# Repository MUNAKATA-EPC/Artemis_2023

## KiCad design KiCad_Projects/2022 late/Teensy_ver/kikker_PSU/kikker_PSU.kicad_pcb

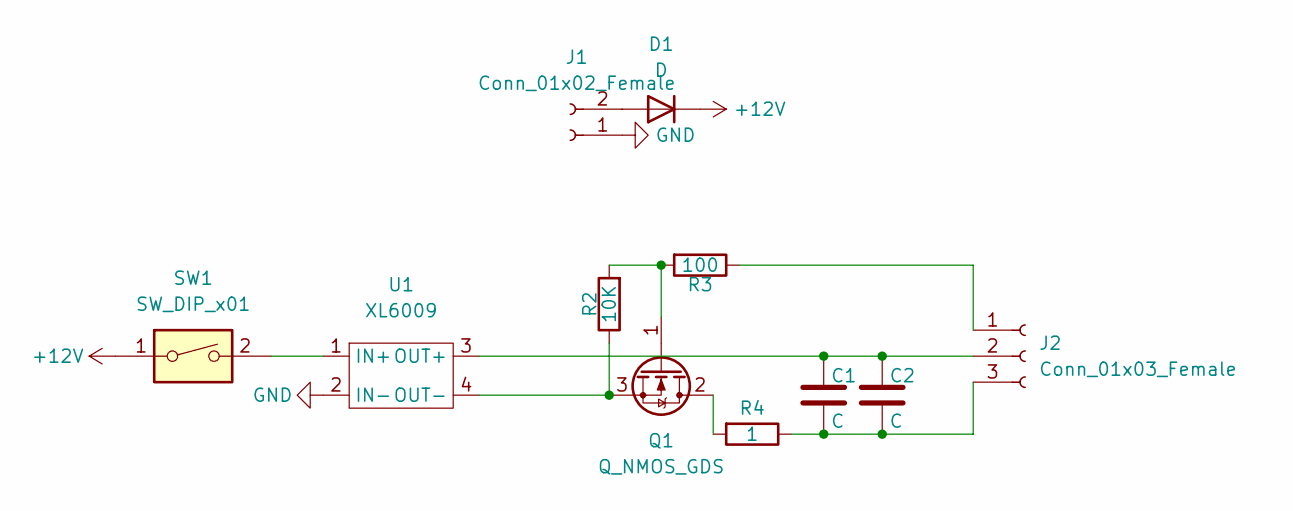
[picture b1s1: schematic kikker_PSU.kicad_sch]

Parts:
C1, C2: C; C_Radial_D16.0mm_H31.5mm_P7.50mm
D1: D; D_DO-15_P10.16mm_Horizontal
J1: Conn_01x02_Female; JST_XH_B2B-XH-A_1x02_P2.50mm_Vertical
J2: Conn_01x03_Female; JST_XH_B3B-XH-A_1x03_P2.50mm_Vertical
Q1: Q_NMOS_GDS; K15A20D
R2: 10K; R_Axial_DIN0204_L3.6mm_D1.6mm_P5.08mm_Horizontal
R3: 100; R_Axial_DIN0204_L3.6mm_D1.6mm_P5.08mm_Horizontal
R4: 1; 5W 1Ω sement
SW1: SW_DIP_x01; 2MS1T2B4M2QES
U1: XL6009

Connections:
+12V: D1.1 (K), SW1.1
GND: J1.1, U1.2 (IN-)
unnamed: C1.1, C2.1, J2.2, U1.3 (OUT+)
unnamed: C1.2, C2.2, J2.3, R4.1
unnamed: D1.2 (A), J1.2
unnamed: J2.1, R3.1
unnamed: Q1.1 (G), R2.2, R3.2
unnamed: Q1.2 (D), R4.2
unnamed: Q1.3 (S), R2.1, U1.4 (OUT-)
unnamed: SW1.2, U1.1 (IN+)

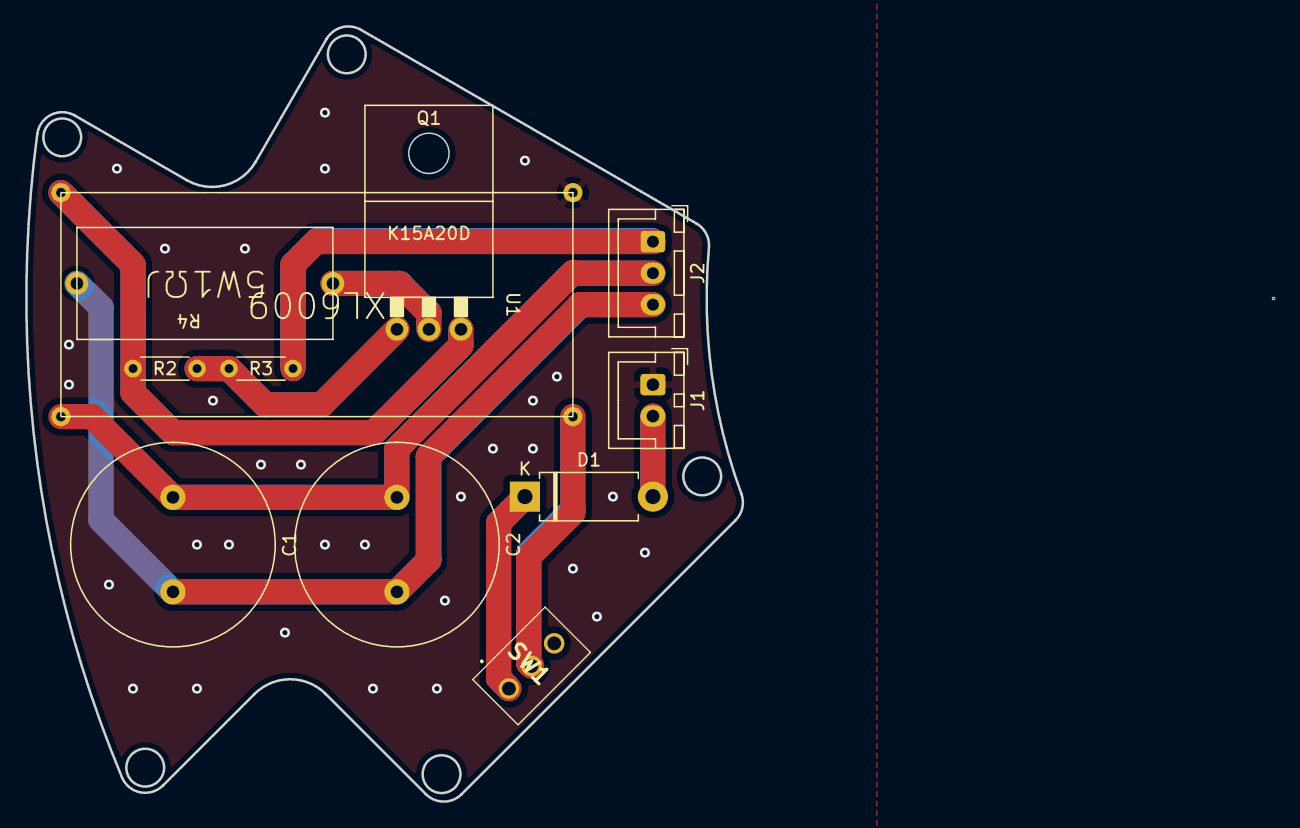
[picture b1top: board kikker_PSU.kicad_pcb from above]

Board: 2 copper layers, 56.9 x 61.5 mm, 11 parts (0 on the bottom side), 10 nets.

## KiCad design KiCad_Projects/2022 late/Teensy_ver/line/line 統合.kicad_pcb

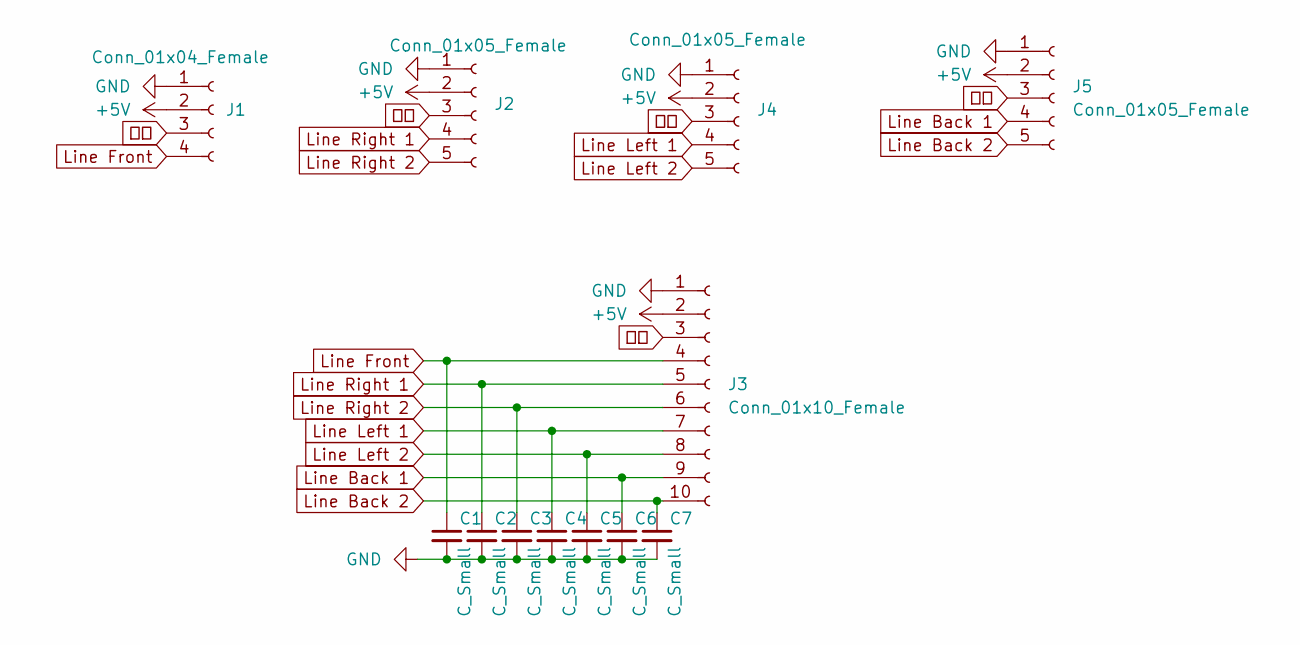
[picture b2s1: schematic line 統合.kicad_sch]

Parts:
C1, C2, C3, C4, C5, C6, C7: C_Small; C_Disc_D3.0mm_W1.6mm_P2.50mm
J1: Conn_01x04_Female; PinSocket_1x04_P2.54mm_Horizontal
J2, J4, J5: Conn_01x05_Female; PinSocket_1x05_P2.54mm_Horizontal
J3: Conn_01x10_Female; JST_XH_B10B-XH-A_1x10_P2.50mm_Vertical

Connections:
Line Left 1: C4.1, J3.7, J4.4
+5V: J1.2, J2.2, J3.2, J4.2, J5.2
GND: C1.2, C2.2, C3.2, C4.2, C5.2, C6.2, C7.2, J1.1, J2.1, J3.1, J4.1, J5.1
Line Back 1: C6.1, J3.9, J5.4
Line Back 2: C7.1, J3.10, J5.5
Line Front: C1.1, J1.4, J3.4
Line Left 2: C5.1, J3.8, J4.5
Line Right 1: C2.1, J2.4, J3.5
Line Right 2: C3.1, J2.5, J3.6
可変: J1.3, J2.3, J3.3, J4.3, J5.3

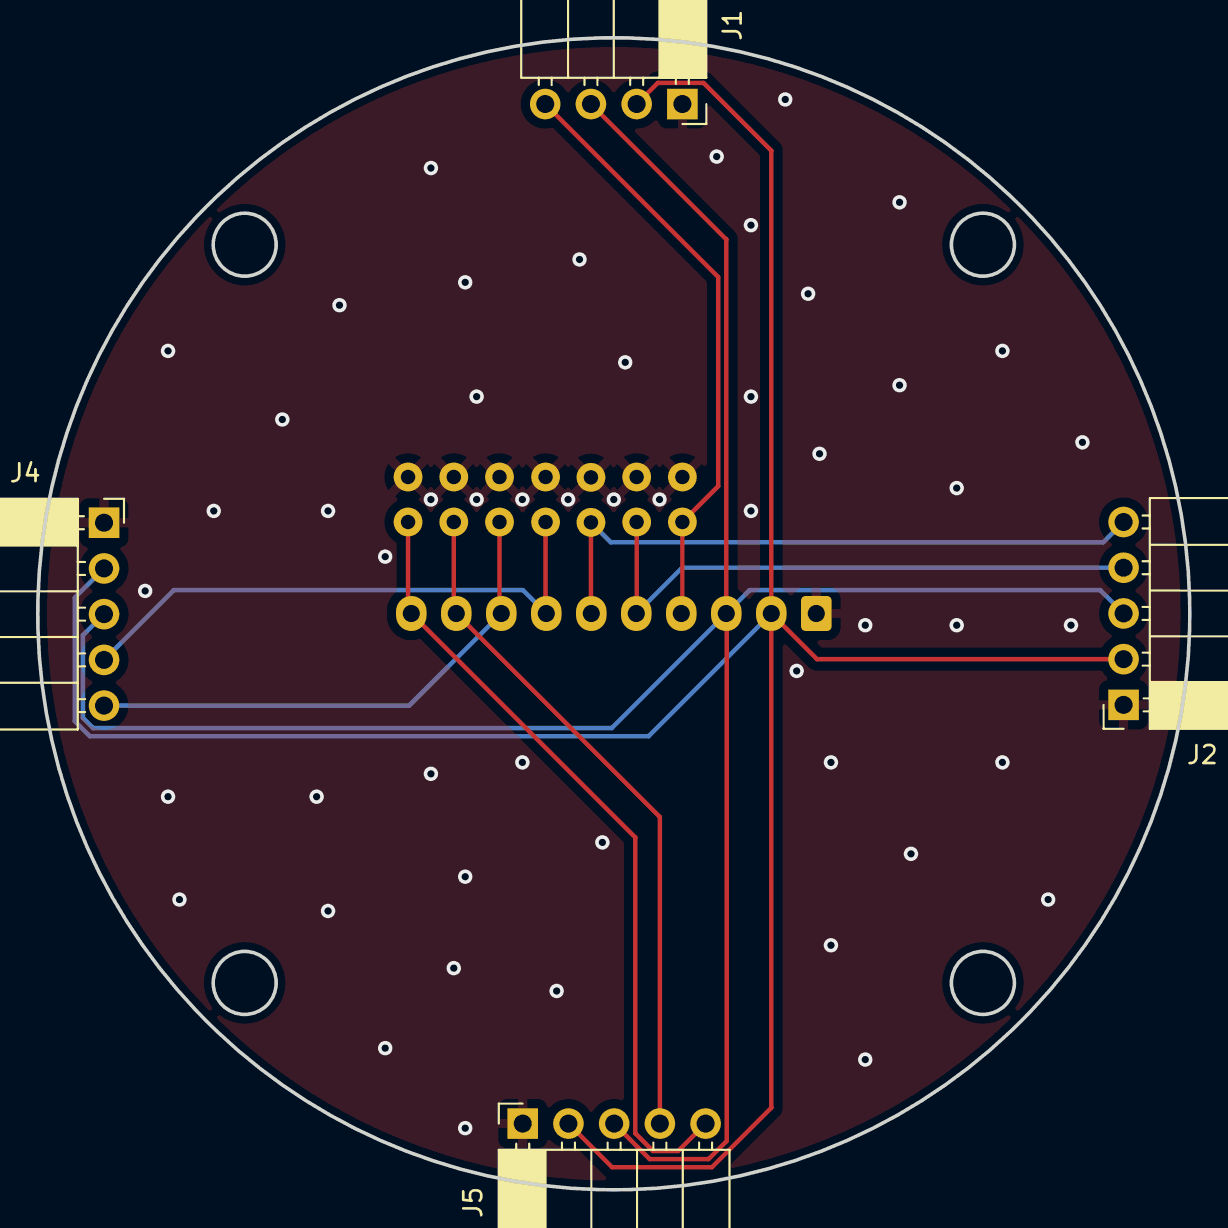
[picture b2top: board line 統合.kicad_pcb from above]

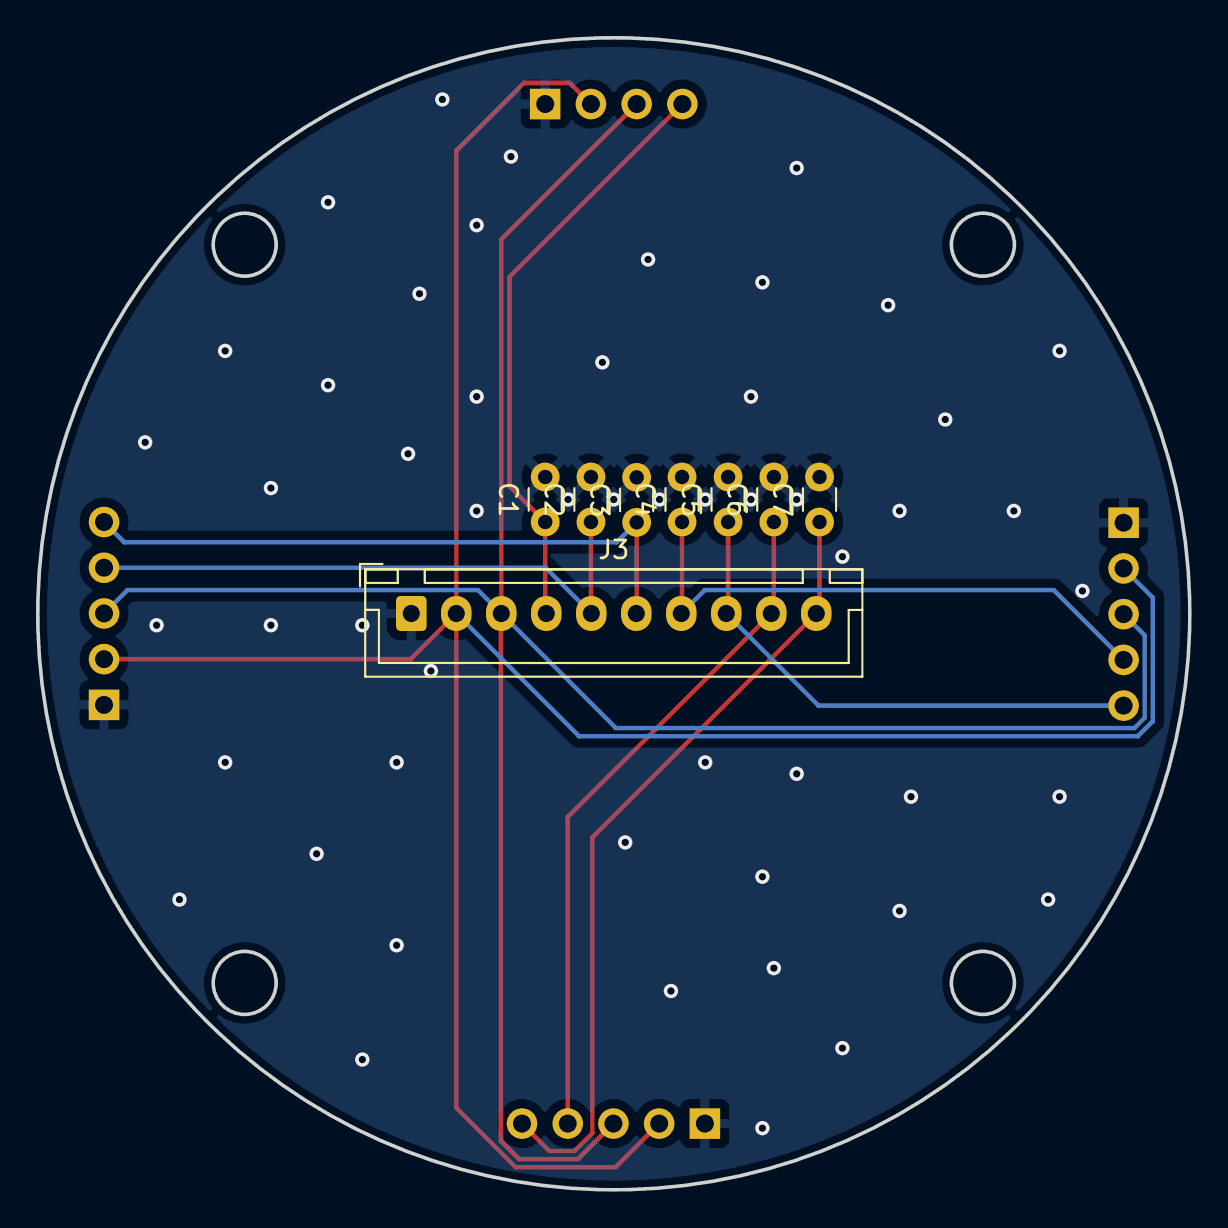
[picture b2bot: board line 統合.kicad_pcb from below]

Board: 2 copper layers, 64.0 x 64.0 mm, 12 parts (8 on the bottom side), 10 nets.

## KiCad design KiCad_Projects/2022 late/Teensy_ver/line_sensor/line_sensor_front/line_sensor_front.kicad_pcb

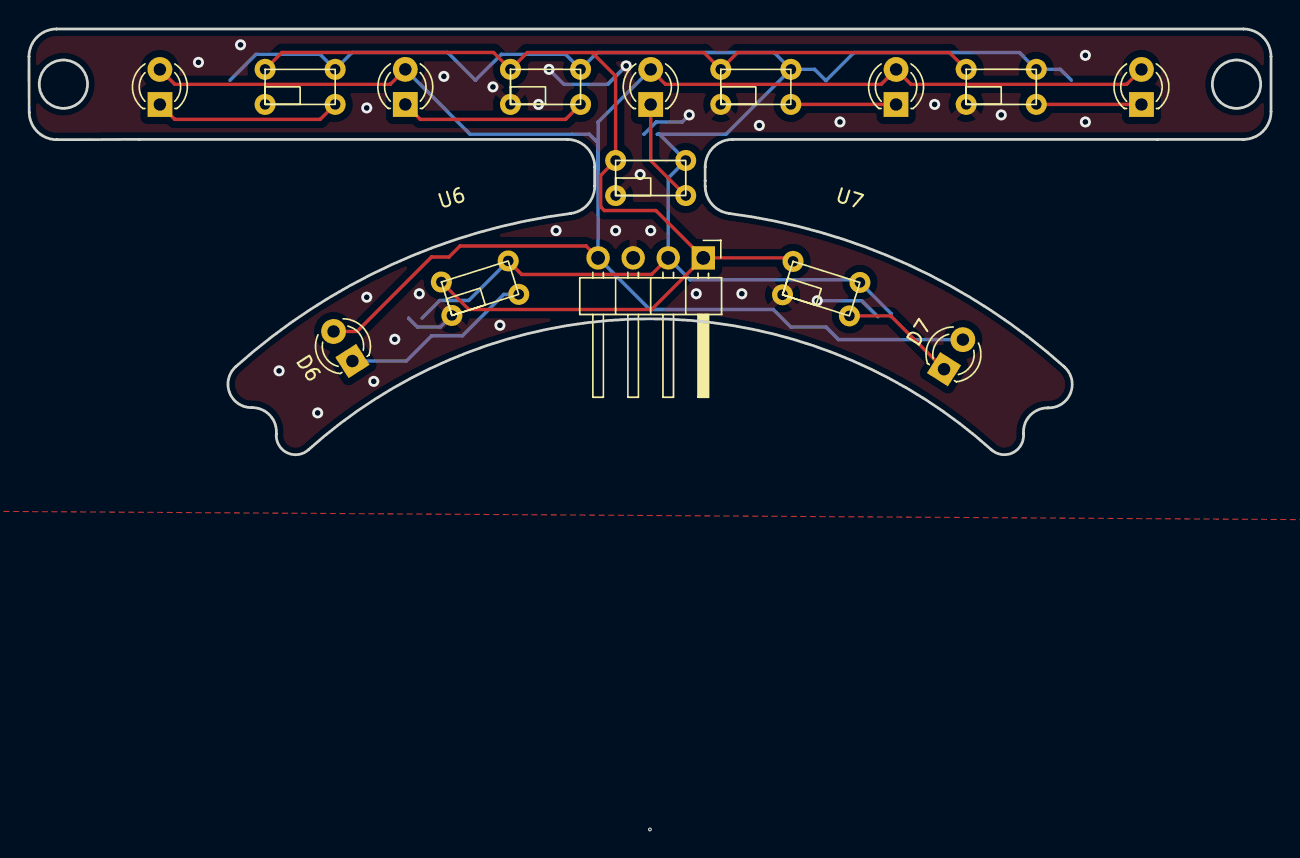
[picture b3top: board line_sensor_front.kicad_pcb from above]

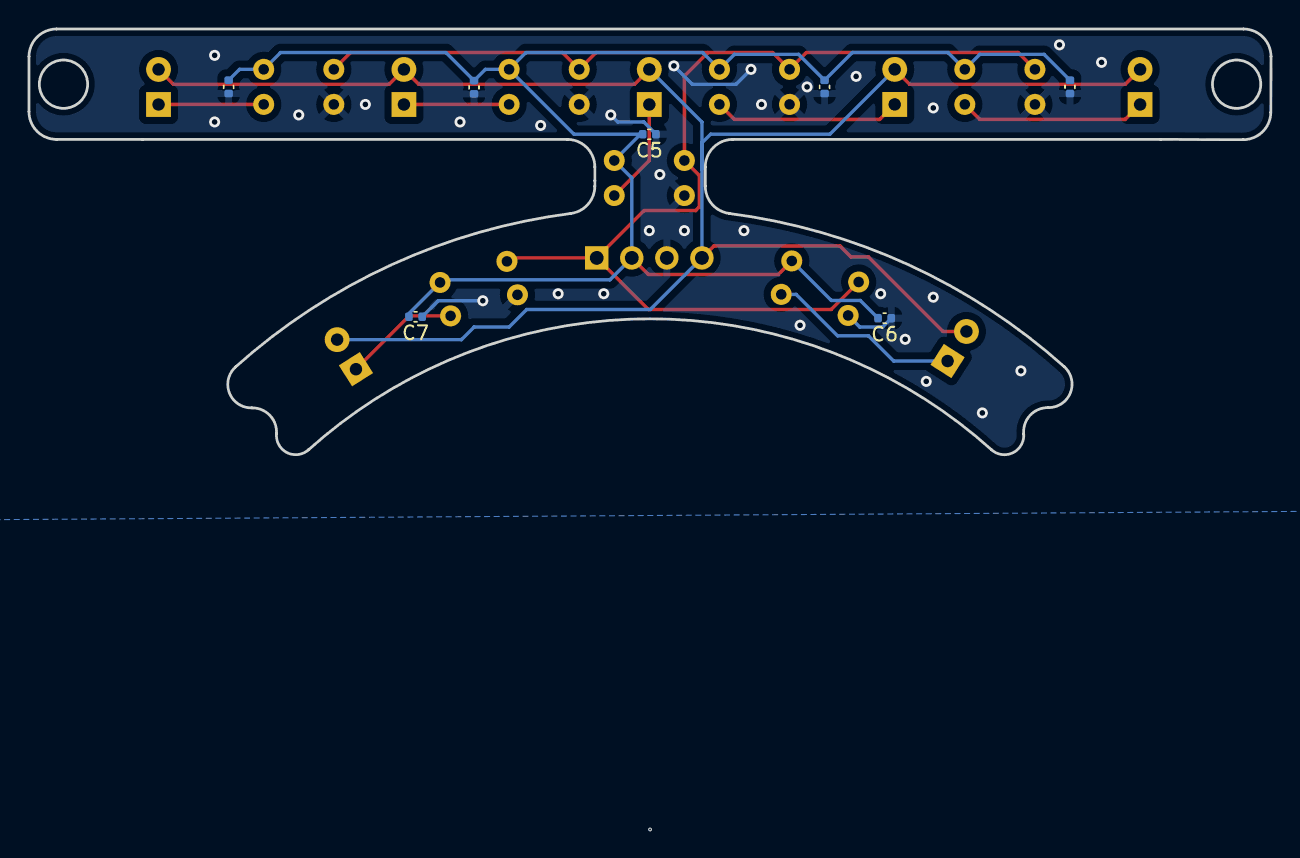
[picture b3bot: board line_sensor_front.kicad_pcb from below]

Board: 2 copper layers, 90.0 x 30.8 mm, 22 parts (7 on the bottom side), 11 nets.

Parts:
C1, C2, C3, C4, C5, C6, C7: C_Small; C_0402_1005Metric
D1, D2, D3, D4, D5, D6, D7: LED; LED_D3.0mm_Clear
J1: Conn_01x04_Female; PinHeader_1x04_P2.54mm_Horizontal
U1, U2, U3, U4, U5, U6, U7: Line_sennsor

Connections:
unnamed: C1.1, C2.1, C3.1, C4.1, C5.1, C6.1, C7.1, J1.3, U1.4 (GND), U2.4 (GND), U3.4 (GND), U4.4 (GND), U5.4 (GND), U6.4 (GND), U7.4 (GND)
unnamed: C1.2, C2.2, C3.2, C4.2, C5.2, C6.2, C7.2, J1.2, U1.2 (VCC), U2.2 (VCC), U3.2 (VCC), U4.2 (VCC), U5.2 (VCC), U6.2 (VCC), U7.2 (VCC)
unnamed: D1.1 (K), U1.1 (K(-))
unnamed: D1.2 (A), D2.2 (A), D3.2 (A), D4.2 (A), D5.2 (A), D6.2 (A), D7.2 (A), J1.4
unnamed: D2.1 (K), U2.1 (K(-))
unnamed: D3.1 (K), U3.1 (K(-))
unnamed: D4.1 (K), U4.1 (K(-))
unnamed: D5.1 (K), U5.1 (K(-))
unnamed: D6.1 (K), U6.1 (K(-))
unnamed: J1.1, U1.3 (VOUT), U2.3 (VOUT), U3.3 (VOUT), U4.3 (VOUT), U5.3 (VOUT), U6.3 (VOUT), U7.3 (VOUT)
unnamed: D7.1 (K), U7.1 (K(-))

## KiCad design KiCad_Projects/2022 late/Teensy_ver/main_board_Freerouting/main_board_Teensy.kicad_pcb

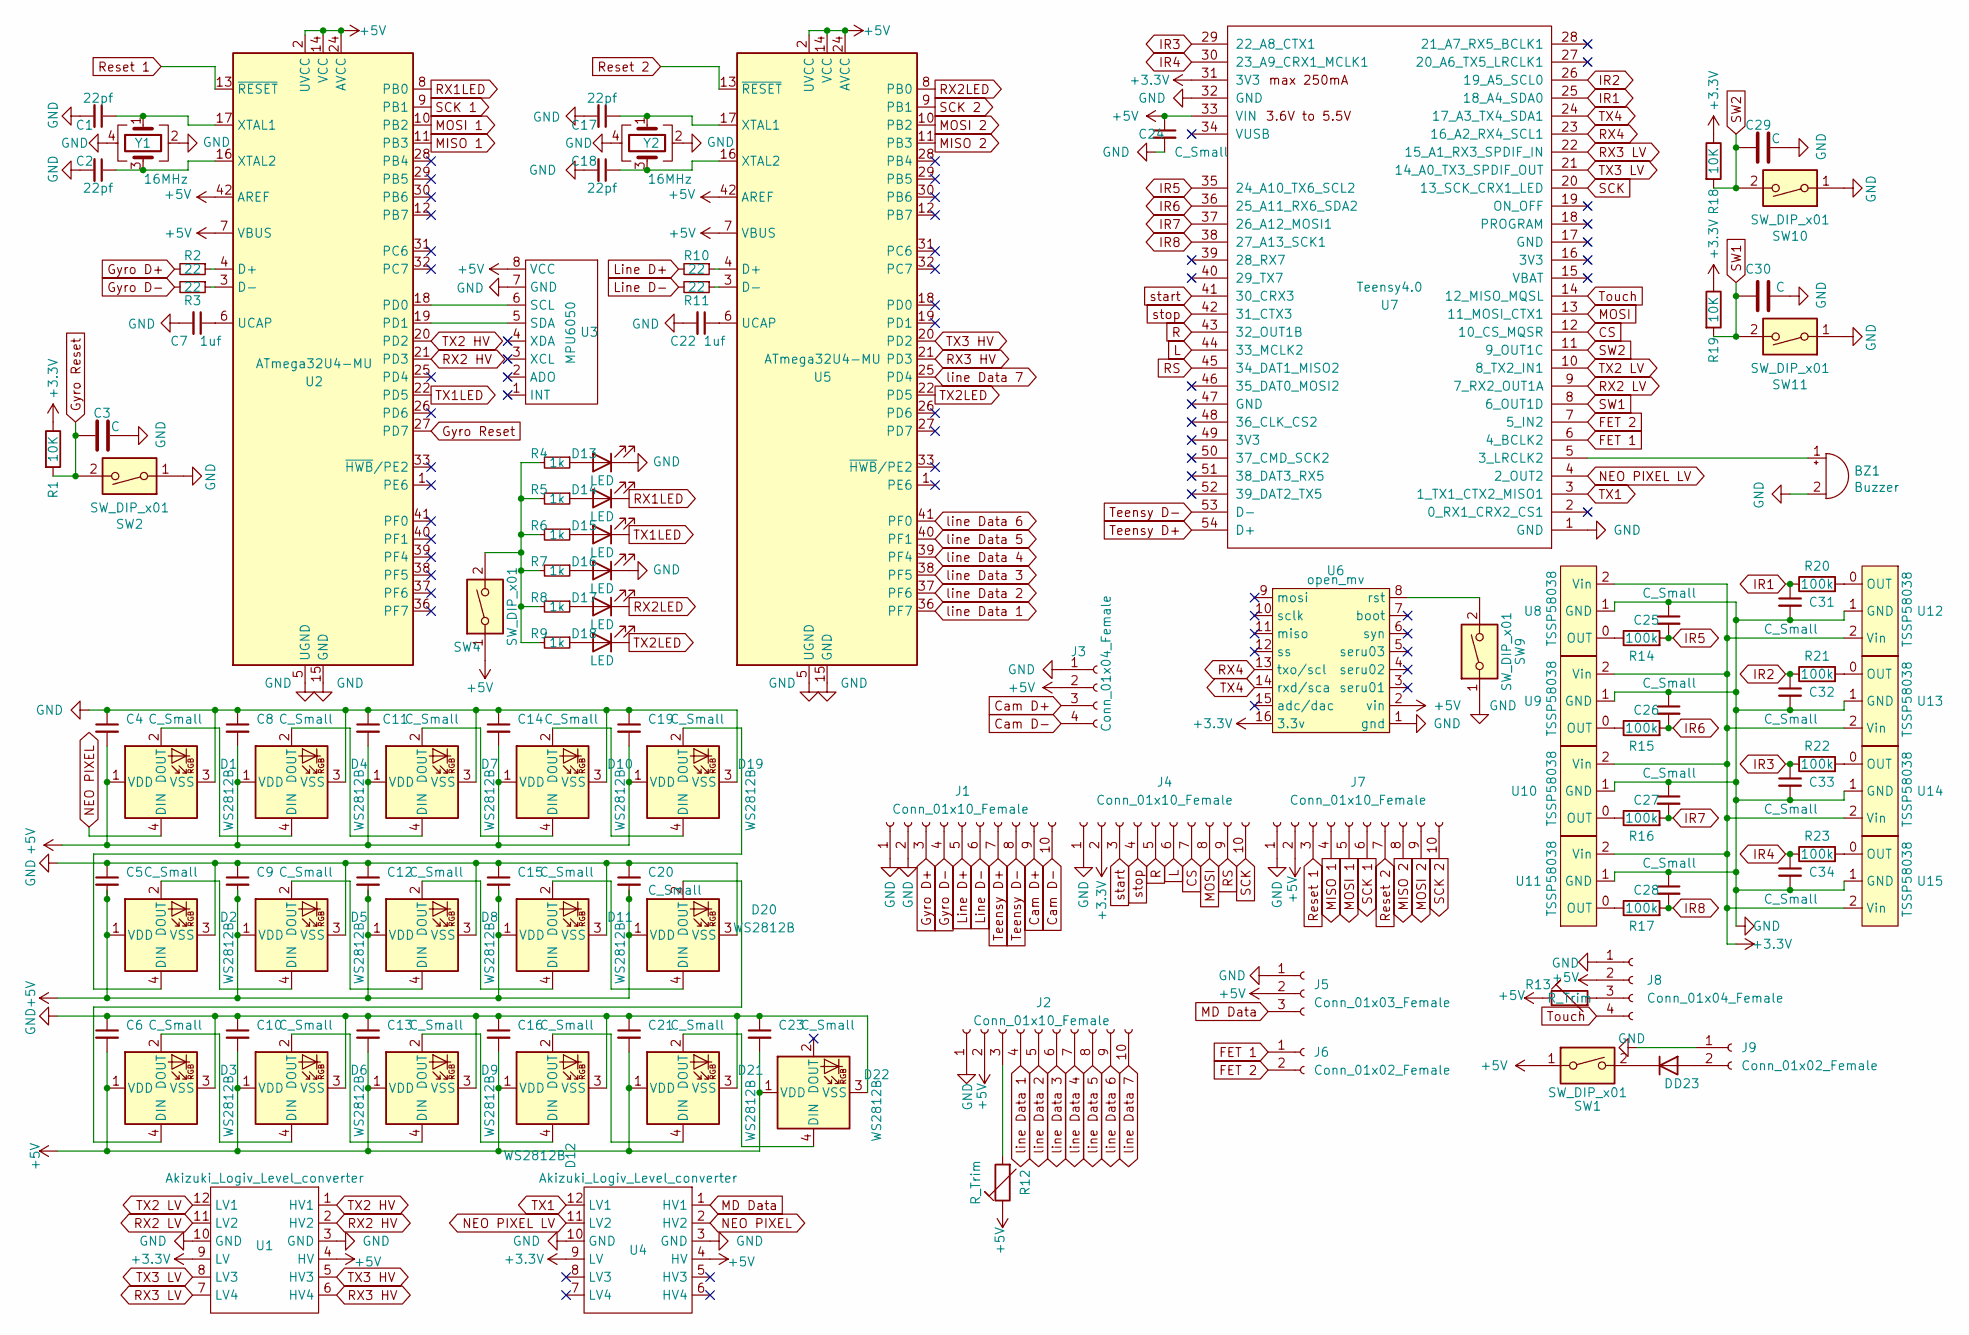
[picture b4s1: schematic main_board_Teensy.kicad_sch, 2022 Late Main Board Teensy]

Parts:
BZ1: Buzzer; Buzzer_12x9.5RM7.6
C1, C2, C17, C18: 22pf; C_0402_1005Metric; LCSC C1555
C3, C29, C30: C; C_0402_1005Metric; LCSC C507422
C4, C5, C6, C8, C9, C10, C11, C12, C13, C14, C15, C16, C19, C20, C21, C23, C24, C25, C26, C27, C28, C31, C32, C33, C34: C_Small; C_0402_1005Metric; LCSC C507422
C7, C22: 1uf; C_0402_1005Metric; LCSC C52923
D1, D2, D3, D5, D6, D7, D8, D9, D10, D11, D12, D19, D20, D21, D22: WS2812B; LED_WS2812B_PLCC4_5.0x5.0mm_P3.2mm; LCSC C2761795
D4: WS2812B; LED_WS2812B_PLCC4_5.0x5.0mm_P3.2mm
D13, D14, D15, D16, D17, D18: LED; LED_0402_1005Metric; LCSC C130725
D23: D; D_A-405_P7.62mm_Horizontal
J1, J4, J7: Conn_01x10_Female; PinHeader_1x10_P2.54mm_Vertical
J2: Conn_01x10_Female; JST_XH_S10B-XH-A-1_1x10_P2.50mm_Horizontal
J3: Conn_01x04_Female; PinHeader_1x04_P2.54mm_Vertical
J5: Conn_01x03_Female; JST_XH_B3B-XH-A_1x03_P2.50mm_Vertical
J6, J9: Conn_01x02_Female; JST_XH_B2B-XH-A_1x02_P2.50mm_Vertical
J8: Conn_01x04_Female; JST_XH_B4B-XH-A_1x04_P2.50mm_Vertical
R1, R18, R19: 10K; R_0402_1005Metric; LCSC C269674
R2, R3, R10, R11: 22; R_0402_1005Metric; LCSC C25092
R4, R5, R6, R7, R8, R9: 1k; R_0402_1005Metric; LCSC C11702
R12, R13: R_Trim; 可変抵抗(小)
R14, R15, R16, R17, R20, R21, R22, R23: 100k; R_0402_1005Metric; LCSC C269673
SW1, SW4: SW_DIP_x01; 2MS1T2B4M2QES
SW2, SW9, SW10, SW11: SW_DIP_x01; SW_PUSH_6mm_H5mm
U1, U4: Akizuki_Logiv_Level_converter; Akizuki_Logic_Level_converter
U2, U5: ATmega32U4-MU; QFN-44-1EP_7x7mm_P0.5mm_EP5.2x5.2mm; LCSC C112161
U3: MPU6050
U6: open_mv; OpenMV
U7: Teensy4.0; Teensy_Brakeout
U8, U9, U10, U11, U12, U13, U14, U15: TSSP58038; TSSP58038_IR
Y1, Y2: 16MHz; Crystal_SMD_3225-4Pin_3.2x2.5mm; LCSC C164049

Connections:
+3V3: J4.2, R1.1, R18.1, R19.1, U1.9 (LV), U4.9 (LV), U6.16 (3.3v), U7.31 (3V3), U8.2 (Vin), U9.2 (Vin), U10.2 (Vin), U11.2 (Vin), U12.2 (Vin), U13.2 (Vin), U14.2 (Vin), U15.2 (Vin)
+5V: C4.2, C5.2, C6.2, C8.2, C9.2, C10.2, C11.2, C12.2, C13.2, C14.2, C15.2, C16.2, C19.2, C20.2, C21.2, C23.2, C24.1, D1.1 (VDD), D2.1 (VDD), D3.1 (VDD), D4.1 (VDD), D5.1 (VDD), D6.1 (VDD), D7.1 (VDD), D8.1 (VDD), D9.1 (VDD), D10.1 (VDD), D11.1 (VDD), D12.1 (VDD), D19.1 (VDD), D20.1 (VDD), D21.1 (VDD), D22.1 (VDD), J2.2, J3.2, J5.2, J7.2, J8.2, R12.1, R13.1, SW1.1, SW4.1, U1.4 (HV), U2.2 (UVCC), U2.7 (VBUS), U2.14 (VCC), U2.24 (AVCC), U2.34 (VCC), U2.42 (AREF), U2.44 (AVCC), U3.8 (VCC), U4.4 (HV), U5.2 (UVCC), U5.7 (VBUS), U5.14 (VCC), U5.24 (AVCC), U5.34 (VCC), U5.42 (AREF), U5.44 (AVCC), U6.2 (vin), U7.33 (VIN)
CS: J4.7, U7.12 (10_CS_MQSR)
Cam D+: J1.9, J3.3
Cam D-: J1.10, J3.4
FET 1: J6.1, U7.6 (4_BCLK2)
FET 2: J6.2, U7.7 (5_IN2)
GND: BZ1.2 (+), C1.2, C2.2, C3.2, C4.1, C5.1, C6.1, C7.2, C8.1, C9.1, C10.1, C11.1, C12.1, C13.1, C14.1, C15.1, C16.1, C17.2, C18.2, C19.1, C20.1, C21.1, C22.2, C23.1, C24.2, C25.1, C26.1, C27.1, C28.1, C29.2, C30.2, C31.2, C32.2, C33.2, C34.2, D1.3 (VSS), D2.3 (VSS), D3.3 (VSS), D4.3 (VSS), D5.3 (VSS), D6.3 (VSS), D7.3 (VSS), D8.3 (VSS), D9.3 (VSS), D10.3 (VSS), D11.3 (VSS), D12.3 (VSS), D13.1 (K), D16.1 (K), D19.3 (VSS), D20.3 (VSS), D21.3 (VSS), D22.3 (VSS), J1.1, J1.2, J2.1, J3.1, J4.1, J5.1, J7.1, J8.1, J9.1, SW2.1, SW9.1, SW10.1, SW11.1, U1.3 (GND), U1.10 (GND), U2.5 (UGND), U2.15 (GND), U2.23 (GND), U2.35 (GND), U2.43 (GND), U2.45 (GND), U3.7 (GND), U4.3 (GND), U4.10 (GND), U5.5 (UGND), U5.15 (GND), U5.23 (GND), U5.35 (GND), U5.43 (GND), U5.45 (GND), U6.1 (gnd), U7.1 (GND), U7.32 (GND), U8.1 (GND), U9.1 (GND), U10.1 (GND), U11.1 (GND), U12.1 (GND), U13.1 (GND), U14.1 (GND), U15.1 (GND), Y1.2, Y1.4, Y2.2, Y2.4; also elsewhere on the board
Gyro D+: J1.3, R2.2
Gyro D-: J1.4, R3.2
Gyro Reset: C3.1, R1.2, SW2.2, U2.27 (PD7); also elsewhere on the board
IR1: C31.1, R20.1, U7.25 (18_A4_SDA0)
IR2: C32.1, R21.1, U7.26 (19_A5_SCL0)
IR3: C33.1, R22.1, U7.29 (22_A8_CTX1)
IR4: C34.1, R23.1, U7.30 (23_A9_CRX1_MCLK1)
IR5: C25.2, R14.2, U7.35 (24_A10_TX6_SCL2)
IR6: C26.2, R15.2, U7.36 (25_A11_RX6_SDA2)
IR7: C27.2, R16.2, U7.37 (26_A12_MOSI1)
IR8: C28.2, R17.2, U7.38 (27_A13_SCK1)
L: J4.6, U7.44 (33_MCLK2)
Line D+: J1.5, R10.2
Line D-: J1.6, R11.2
MD Data: J5.3, U4.1 (HV1)
MISO 1: J7.4, U2.11 (PB3)
MISO 2: J7.8, U5.11 (PB3)
MOSI: J4.8, U7.13 (11_MOSI_CTX1)
MOSI 1: J7.5, U2.10 (PB2)
MOSI 2: J7.9, U5.10 (PB2)
NEO PIXEL: D1.4 (DIN), U4.2 (HV2)
NEO PIXEL LV: U4.11 (LV2), U7.4 (2_OUT2)
unnamed: BZ1.1 (-), U7.5 (3_LRCLK2)
unnamed: C1.1, U2.17 (XTAL1), Y1.1
unnamed: C2.1, U2.16 (XTAL2), Y1.3
unnamed: C7.1, U2.6 (UCAP)
unnamed: C17.1, U5.17 (XTAL1), Y2.1
unnamed: C18.1, U5.16 (XTAL2), Y2.3
unnamed: C22.1, U5.6 (UCAP)
unnamed: D1.2 (DOUT), D4.4 (DIN)
unnamed: D2.2 (DOUT), D5.4 (DIN)
unnamed: D3.2 (DOUT), D6.4 (DIN)
unnamed: D4.2 (DOUT), D7.4 (DIN)
unnamed: D5.2 (DOUT), D8.4 (DIN)
unnamed: D6.2 (DOUT), D9.4 (DIN)
unnamed: D10.2 (DOUT), D19.4 (DIN)
unnamed: D7.2 (DOUT), D10.4 (DIN)
unnamed: D11.2 (DOUT), D20.4 (DIN)
unnamed: D8.2 (DOUT), D11.4 (DIN)
unnamed: D12.2 (DOUT), D21.4 (DIN)
unnamed: D9.2 (DOUT), D12.4 (DIN)
unnamed: D13.2 (A), R4.1
unnamed: D14.2 (A), R5.1
unnamed: D15.2 (A), R6.1
unnamed: D16.2 (A), R7.1
unnamed: D17.2 (A), R8.1
unnamed: D18.2 (A), R9.1
unnamed: D2.4 (DIN), D19.2 (DOUT)
unnamed: D3.4 (DIN), D20.2 (DOUT)
unnamed: D21.2 (DOUT), D22.4 (DIN)
unnamed: D23.1 (K), SW1.2
unnamed: D23.2 (A), J9.2
unnamed: J2.3, R12.2
unnamed: J8.3, R13.2
unnamed: R2.1, U2.4 (D+)
unnamed: R3.1, U2.3 (D-)
unnamed: R4.2, R5.2, R6.2, R7.2, R8.2, R9.2, SW4.2
unnamed: R10.1, U5.4 (D+)
unnamed: R11.1, U5.3 (D-)
unnamed: R14.1, U8.0 (OUT)
unnamed: R15.1, U9.0 (OUT)
unnamed: R16.1, U10.0 (OUT)
unnamed: R17.1, U11.0 (OUT)
unnamed: R20.2, U12.0 (OUT)
unnamed: R21.2, U13.0 (OUT)
unnamed: R22.2, U14.0 (OUT)
unnamed: R23.2, U15.0 (OUT)
unnamed: U2.18 (PD0), U3.6 (SCL)
unnamed: U2.19 (PD1), U3.5 (SDA)
unnamed 77: SW9.2, U6.8 (rst); also elsewhere on the board
R: J4.5, U7.43 (32_OUT1B)
RS: J4.9, U7.45 (34_DAT1_MISO2)
RX1LED: D14.1 (K), U2.8 (PB0)
RX2 HV: U1.2 (HV2), U2.21 (PD3)
RX2 LV: U1.11 (LV2), U7.9 (7_RX2_OUT1A)
RX2LED: D17.1 (K), U5.8 (PB0)
RX3 HV: U1.6 (HV4), U5.21 (PD3)
RX3 LV: U1.7 (LV4), U7.22 (15_A1_RX3_SPDIF_IN)
RX4: U6.13 (txo/scl), U7.23 (16_A2_RX4_SCL1)
Reset 1: J7.3, U2.13 (~RESET)
Reset 2: J7.7, U5.13 (~RESET)
SCK: J4.10, U7.20 (13_SCK_CRX1_LED)
SCK 1: J7.6, U2.9 (PB1)
SCK 2: J7.10, U5.9 (PB1)
SW1: C30.1, R19.2, SW11.2, U7.8 (6_OUT1D); also elsewhere on the board
SW2: C29.1, R18.2, SW10.2, U7.11 (9_OUT1C)
TX1: U4.12 (LV1), U7.3 (1_TX1_CTX2_MISO1)
TX1LED: D15.1 (K), U2.22 (PD5)
TX2 HV: U1.1 (HV1), U2.20 (PD2)
TX2 LV: U1.12 (LV1), U7.10 (8_TX2_IN1)
TX2LED: D18.1 (K), U5.22 (PD5)
TX3 HV: U1.5 (HV3), U5.20 (PD2)
TX3 LV: U1.8 (LV3), U7.21 (14_A0_TX3_SPDIF_OUT)
TX4: U6.14 (rxd/sca), U7.24 (17_A3_TX4_SDA1)
Teensy D+: J1.7, U7.54 (D+)
Teensy D-: J1.8, U7.53 (D-)
Touch: J8.4, U7.14 (12_MISO_MQSL)
line Data 1: J2.4, U5.36 (PF7)
line Data 2: J2.5, U5.37 (PF6)
line Data 3: J2.6, U5.38 (PF5)
line Data 4: J2.7, U5.39 (PF4)
line Data 5: J2.8, U5.40 (PF1)
line Data 6: J2.9, U5.41 (PF0)
line Data 7: J2.10, U5.25 (PD4)
start: J4.3, U7.41 (30_CRX3)
stop: J4.4, U7.42 (31_CTX3)

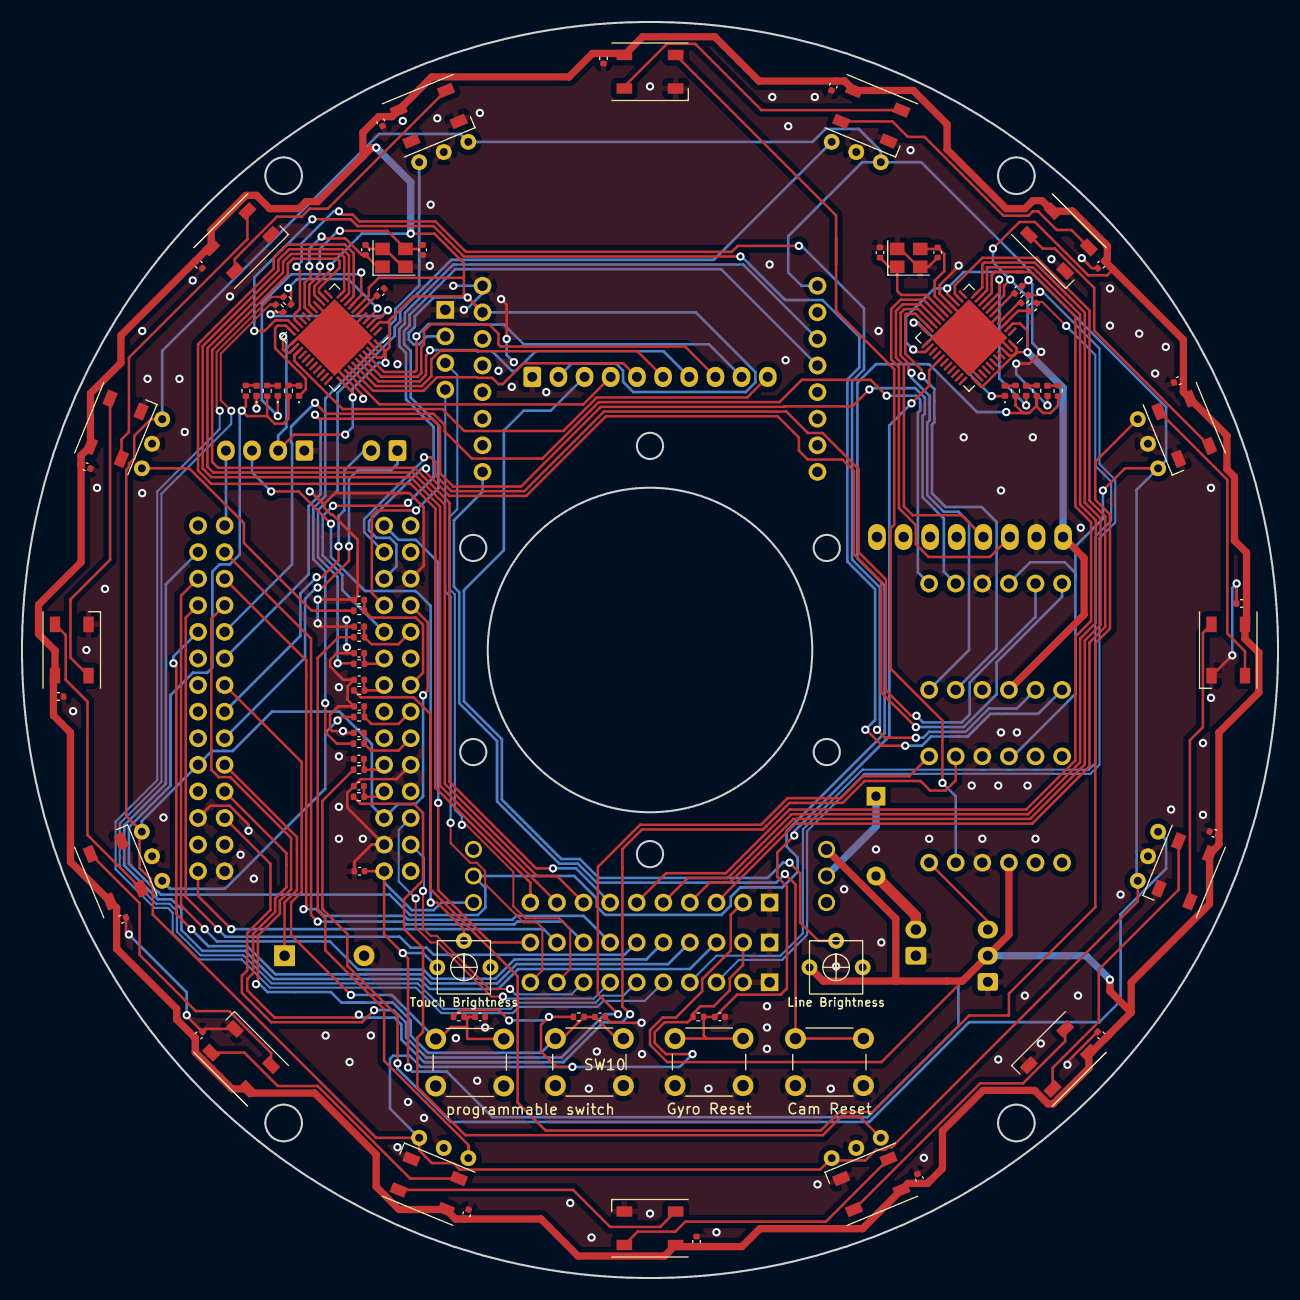
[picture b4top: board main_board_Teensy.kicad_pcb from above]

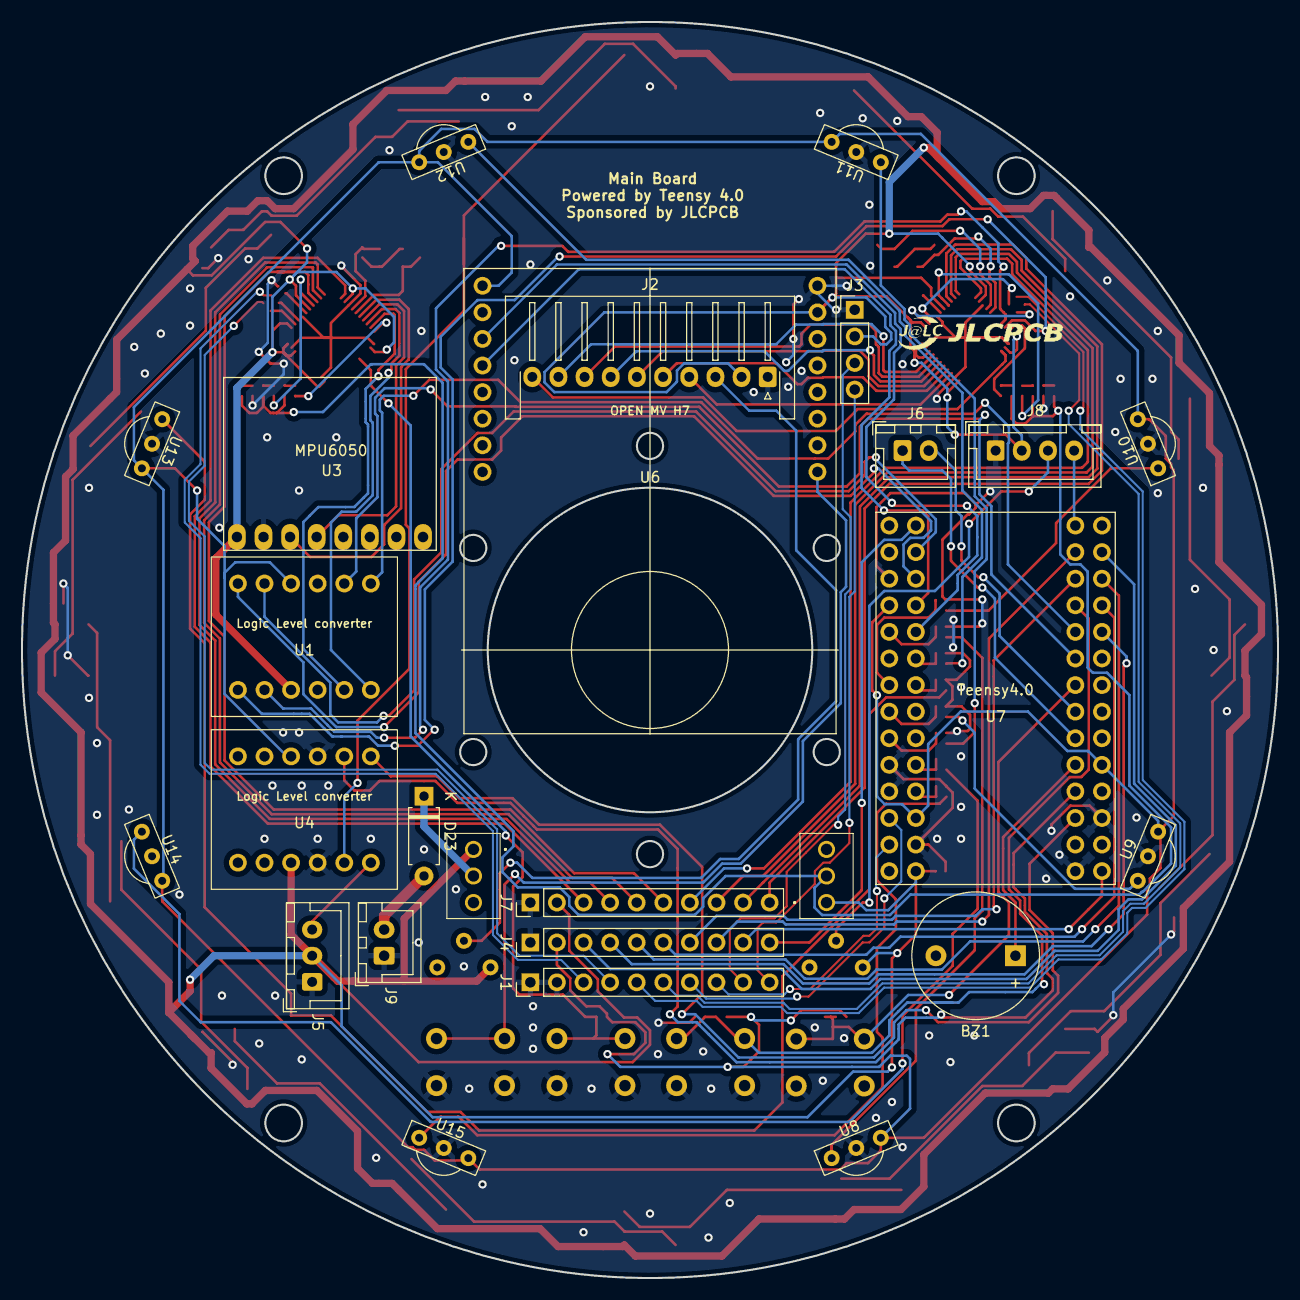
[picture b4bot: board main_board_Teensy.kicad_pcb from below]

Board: 2 copper layers, 120.0 x 120.0 mm, 113 parts (26 on the bottom side), 114 nets.

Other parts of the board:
Cam Reset: SW_DIP_x01; SW_PUSH_6mm_H5mm
Gyro Reset: SW_DIP_x01; SW_PUSH_6mm_H5mm
programmable switch: SW_DIP_x01; SW_PUSH_6mm_H5mm

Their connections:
GND: Cam Reset.1, Gyro Reset.1, programmable switch.1; also elsewhere on the board
Gyro Reset: Gyro Reset.2; also elsewhere on the board
unnamed 77: Cam Reset.2; also elsewhere on the board
SW1: programmable switch.2; also elsewhere on the board
